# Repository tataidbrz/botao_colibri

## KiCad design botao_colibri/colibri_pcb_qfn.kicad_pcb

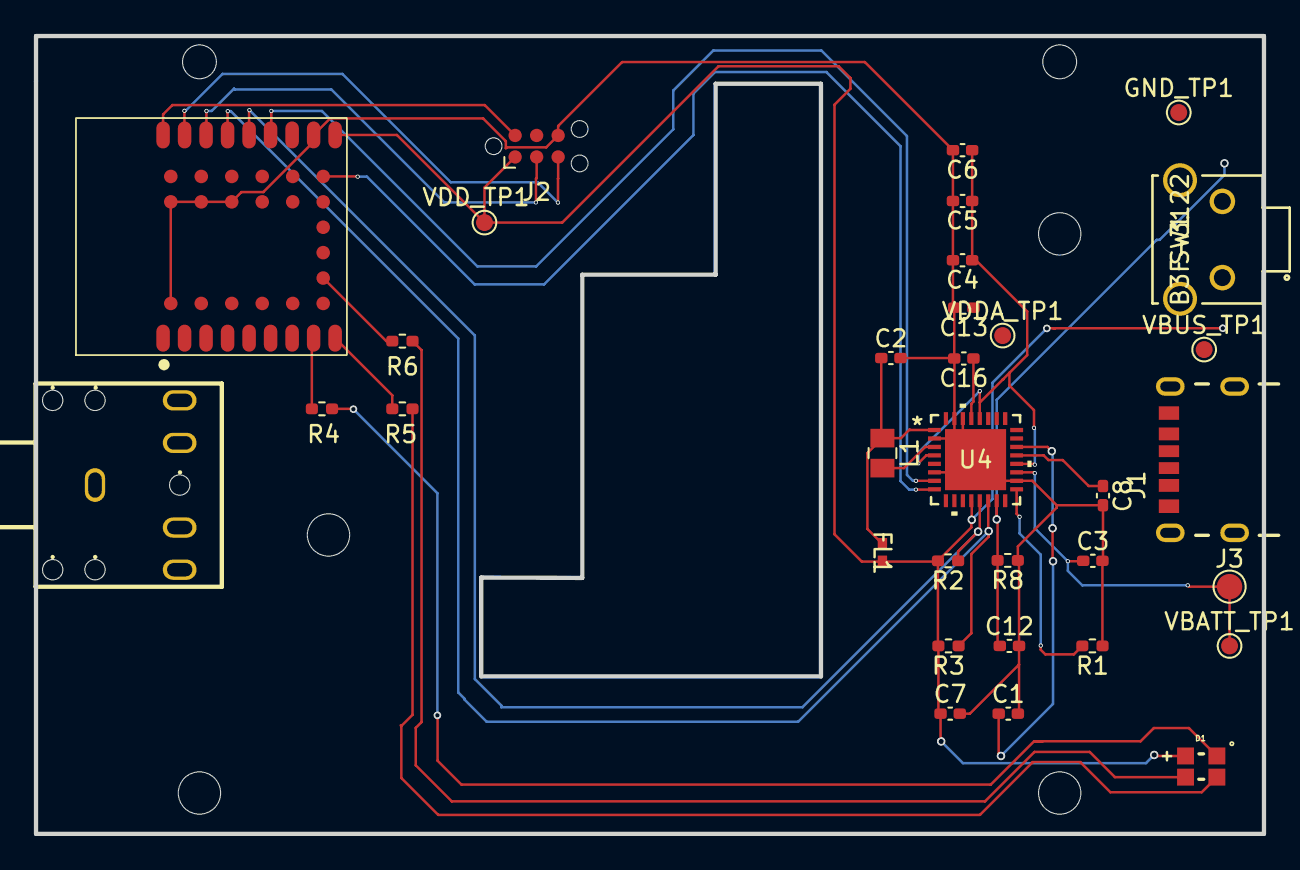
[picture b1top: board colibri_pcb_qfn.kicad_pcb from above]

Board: 2 copper layers, 72.5 x 47.1 mm, 39 parts (0 on the bottom side), 28 nets.

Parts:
C1, C3, C4, C5, C6, C7, C8: C_Small; C_0402_1005Metric_Pad0.74x0.62mm_HandSolder
C2: 10µF; C_0402_1005Metric_Pad0.74x0.62mm_HandSolder
C12, C13: 100nF; C_0402_1005Metric_Pad0.74x0.62mm_HandSolder
C16: 1uF; C_0402_1005Metric_Pad0.74x0.62mm_HandSolder
D1: WL-SFCD_0805
FL1: BLM15AG121SN1D; IND_BLM15_0402_MUR
GND_TP1: TestPoint; TestPoint_Pad_D1.0mm
H1, H2, H3, H4, H5, H6: NPTH
J1: USB4970-00-A_REVA; GCT_USB4970-00-A_REVA
J2: TC2030; Tag-Connect_TC2030-IDC-NL_2x03_P1.27mm_Vertical
J3: Conn_01x02; TestPoint_Pad_D1.5mm
J4: PJ-307C; AUDIO-TH_PJ307C
L1: 2.2µH; LQM21PN2R2MGRD
R1: 360kR; R_0402_1005Metric_Pad0.72x0.64mm_HandSolder
R2, R3: 4.7kR; R_0402_1005Metric_Pad0.72x0.64mm_HandSolder
R4, R5, R6: R_Small; R_0402_1005Metric_Pad0.72x0.64mm_HandSolder
R8: 330kR; R_0402_1005Metric_Pad0.72x0.64mm_HandSolder
SW1: B3F-3122
U1: ME54BS12; ME54BS12_V1.0
U4: NPM1300-QEAA-R7; NPM1300_QFN32_5X5_NOR
VBATT_TP1: TestPoint; TestPoint_Pad_D1.0mm
VBUS_TP1: TestPoint; TestPoint_Pad_D1.0mm
VDDA_TP1: TestPoint; TestPoint_Pad_D1.0mm
VDD_TP1: TestPoint; TestPoint_Pad_D1.0mm

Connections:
+BATT: C3.1, J3.1 (Pin_1_1), U4.19 (VBAT), VBATT_TP1.1 (1_1)
BTN_PWR: C12.1, R8.2, SW1.2, U4.15 (SHPHLD)
GND: C1.2, C2.2, C3.2, C4.2, C5.2, C6.2, C7.2, C8.2, C12.2, C13.2, C16.2, GND_TP1.1 (1_1), J1.A12 (GND), J1.B12 (GND), J1.SH1 (SHELL_GND), J1.SH2 (SHELL_GND), J1.SH3 (SHELL_GND), J1.SH4 (SHELL_GND), J2.6, J4.1, R1.1, R8.1, SW1.4, U1.11 (GND), U1.A1 (GND), U1.A5 (GND), U1.B5 (GND), U1.C5 (GND), U4.2 (PVSS1), U4.6 (PVSS2), U4.18 (NTC), U4.30 (LSIN2/VINLDO2), U4.31 (LSOUT2/VOUTLDO2), U4.33 (AVSS)
I2C_SCL: R3.1, U1.15 (P0.03), U4.14 (SCL)
I2C_SDA: R2.1, U1.14 (P0.02), U4.13 (SDA)
LED_B: R6.2, U1.F2 (P1.04/AIN0)
LED_G: R5.2, U1.9 (P1.05/AIN1)
LED_R: R4.1, U1.8 (P1.06/AIN2)
NPM1300_EN: U1.F6 (P2.04), U4.8 (GPIO1)
NPM1300_INT: U1.13 (P0.01), U4.7 (GPIO0)
NRESET: J2.2, U1.18 (~NRESET)
unnamed: D1.1, R4.2
unnamed: D1.2, R5.1
unnamed: D1.3, R6.1
unnamed: L1.2, U4.3 (SW1)
unnamed: C1.1, U4.22 (VBUSOUT)
unnamed: C2.1, FL1.1, L1.1, U4.1 (VOUT1)
unnamed: R1.2, U4.17 (VSET1)
P2_SENSE: J4.4, U1.6 (P1.03/NFC2)
P2_SQUARE_WAVE: J4.5, U1.5 (P1.14/AIN7)
PVDD: C4.1, C5.1, C6.1, U4.4 (PVDD), U4.20 (VSYS), U4.28 (LSIN1/VINLDO1)
SWCLK: J2.5, U1.17 (SWDCLK)
SWDIO: J2.3, U1.16 (SWDIO)
USB.CC1: J1.A5 (CC1), U4.23 (CC1)
USB.CC2: J1.B5 (CC2), U4.24 (CC2)
USB.VBUS: C8.1, J1.A9 (VBUS), J1.B9 (VBUS), U4.21 (VBUS), VBUS_TP1.1 (1_1)
VDD: C7.1, D1.4, FL1.2, J2.1, R2.2, R3.2, SW1.1, U1.10 (VCC), U4.12 (VDDIO), VDD_TP1.1 (1_1)
VDDA: C13.1, C16.1, U4.29 (LSOUT1/VOUTLDO1), VDDA_TP1.1 (1_1)

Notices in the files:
parts and their libraries:
Copyright 2016 Accelerated Designs. All rights reserved.
